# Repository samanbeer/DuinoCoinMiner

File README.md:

# DuinoCoinMiner

- **What is it?** It is a small PCB board with XIAO ESP32-C3 as main MCU for controlling 6 ATmega328P chips
- **What does it do?** It mines crypto currency called Duino Coin. Which is a specialized coin that can be mined on any device like arduinos and lot more. You read about it on their [site](duinocoin.com)

## Project Gallery

### 3D PCB Renders

### PCB Schematic and layout

### 3D Enclosure (Fusion 360)

*3D printable case made in Fusion 360. All CAD and 3D model files (`.f3z`, `.step`) are in the [`CAD/`](CAD/) folder.*

---

### Required Tools & Materials

- Soldering iron
- Good solder wire
- Solder flux 
- small tweezers for picking small components like resistors and condenzators 
- 3D Printer for printing case from /cad folder

### Assembly Steps

1. **Start with the chips:**
   
   - **ATmega328P-AU** and **BSS138PS** .
   - It is best to solder these first while the board is clear of other bigger things.

2. **SMD Components:**
- - C1–C18, C31, C32 
  - C19–C30 
  - C33
  - R1–R10
3. **Main MCU:**
-     **Seeed Studio XIAO ESP32-C3**.
  - Solder the XIAO directly onto the PCB pads or solder pin headers so you can plug it in(not recommended)
4. **THT Components:**
-     **Crystals:** 20MHz crystals. Clip the leads, and solder from the bottom side.
  - **Switches:** 6x6mm reset buttons. Snap them into their holes and solder.
  - **ISP pin Header:** 2x3 pin header. Solder it to the board.
5. **Enclosure Assembly:**
-     3D print the bottom base (`case.step`) and the lid (`case_lid.step`). Files are in the /CAD folder.
  - Place PCB inside the bottom enclosure, with XIAO USB-C port aligned to the hole, and attach the lid.

---

## Firmware

Firmware files are located in "firmware" folder with README.md that contains guide how to flash the chips correclty and what you will need to install.

## BOM

| Reference               | amount | Value / Component          | Footprint / Package      | Link                                                                                                    | Cost (USD) |
| ----------------------- |:------:|:-------------------------- |:------------------------ |:------------------------------------------------------------------------------------------------------- |:----------:|
| **C1-C18, C31 and C32** | 20     | 100nF 50V                  | 0603 SMD                 | [TME Link](https://www.tme.eu/cz/details/0603b104k500ct/kondenzatory-mlcc-smd/walsin/)                  | $0.40      |
| **C19-C30**             | 12     | 22pF 50V                   | 0603 SMD                 | [TME Link](https://www.tme.eu/cz/details/cc0603jrnpo9bn220/kondenzatory-mlcc-smd/yageo/)                | $0.36      |
| **C33**                 | 1      | 10µF 10V                   | 0603 SMD                 | [TME Link](https://www.tme.eu/cz/details/lmk107bj106maltd/kondenzatory-mlcc-smd/taiyo-yuden/)           | $0.12      |
| **J1**                  | 1      | 2x3 Pin Header             | Pin header 2x03 (2.54mm) | [TME Link](https://www.tme.eu/cz/details/bl2-06g/dutinkove-listy/connfly/)                              | $0.35      |
| **Q1**                  | 1      | BSS138PS mosfet            | SOT-363                  | [TME Link](https://www.tme.eu/cz/details/bss138ps.115/tranzistory-s-polem-n-kanalove-smd/nexperia/)     | $0.45      |
| **R1-R10**              | 10     | 10kΩ                       | 0805 SMD                 | [TME Link](https://www.tme.eu/cz/details/crcw080510k0fkea/rezistory-smd/vishay/)                        | $0.14      |
| **SW1–SW6**             | 6      | Switch (6x6mm, Height=5mm) | SW_PUSH_6mm_H5mm THT     | [TME Link](https://www.tme.eu/cz/details/1825910-6/mikroprepninace-tact-tht/te-connectivity/)           | $0.90      |
| **U1**                  | 1      | Seeed Studio XIAO ESP32-C3 | XIAO DIP/SMD Module      | [TME Link](https://www.tme.eu/cz/details/seeed-113991054/vyvojove-kity-ostatni/seeed-studio/113991054/) | $6.36      |
| **U2-U7**               | 6      | ATmega328P-AU (**20mHz**)  | TQFP-32                  | [TME Link](https://www.tme.eu/cz/details/atmega328p-au/mikrokontrolery-avr/microchip-technology/)       | $14.70     |
| **Y1-Y6**               | 6      | 20MHz Quartz Crystal       | HC-49/U THT              | [TME Link](https://www.tme.eu/cz/details/49-20.000maaj-b/krystalove-rezonatory-tht/qst/)                | $1.80      |
| **PCB**                 | 1      | 2 Layers                   |                          | [JLCPCB](https://jlcpcb.com)                                                                            | ±$14       |
| **Shipping**            |        | Total Shipping             |                          | TME and JLCPCB                                                                                          | $12.9      |
| **Total**               |        |                            |                          |                                                                                                         | **52.48**  |

JLCPCB cart:

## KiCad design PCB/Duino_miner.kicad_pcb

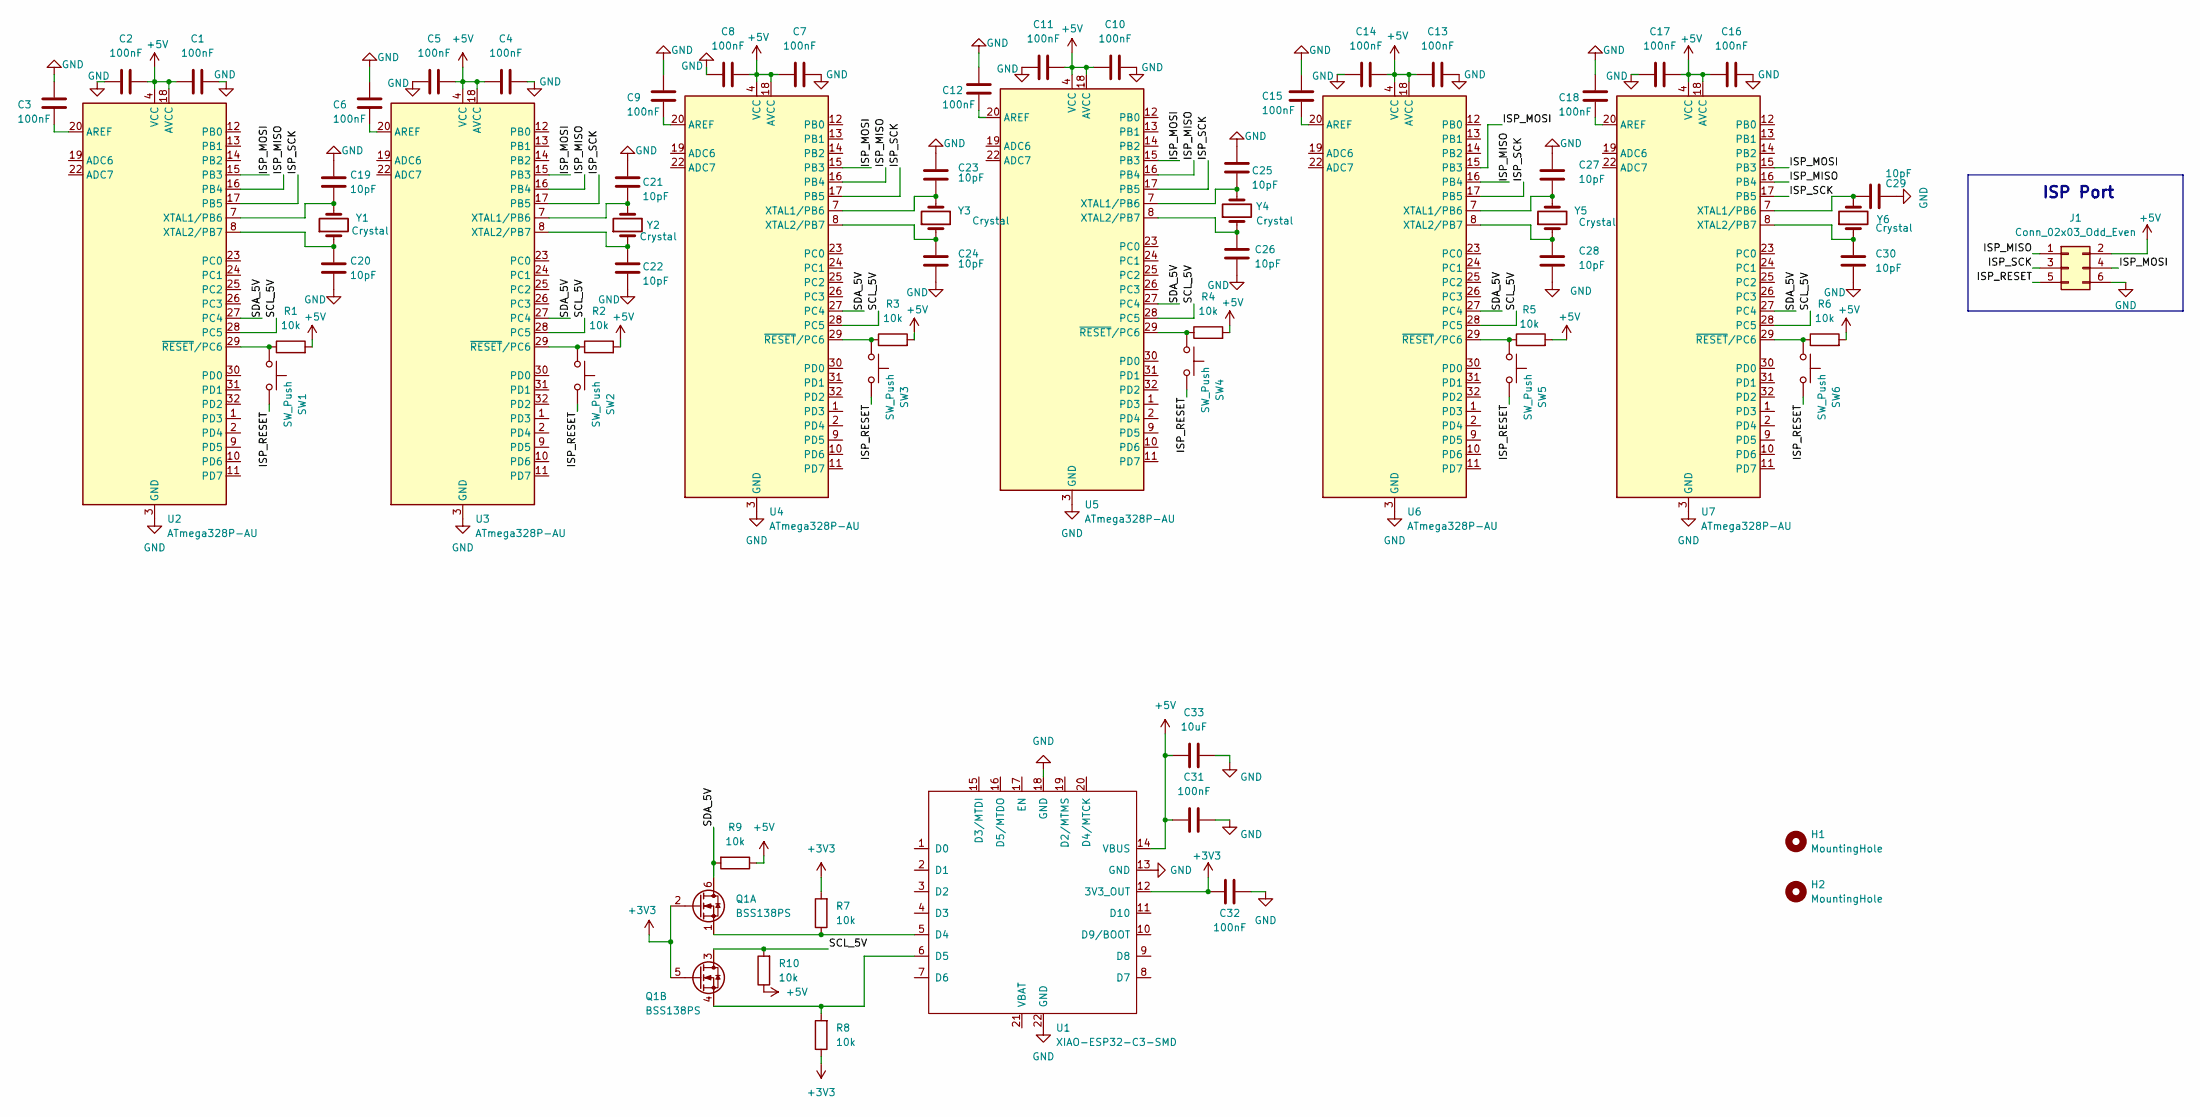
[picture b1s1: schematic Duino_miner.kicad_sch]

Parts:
C1, C2, C3, C4, C5, C6, C7, C8, C9, C10, C11, C12, C13, C14, C15, C16, C17, C18, C31, C32: 100nF; C_0603_1608Metric_Pad1.08x0.95mm_HandSolder
C19, C20, C21, C22, C23, C24, C25, C26, C27, C28, C29, C30: 10pF; C_0603_1608Metric_Pad1.08x0.95mm_HandSolder
C33: 10uF; C_0603_1608Metric_Pad1.08x0.95mm_HandSolder
H1, H2: MountingHole; MountingHole_2mm
J1: Conn_02x03_Odd_Even; PinSocket_2x03_P2.54mm_Vertical
Q1: BSS138PS; SOT-363_SC-70-6
R1, R2, R3, R4, R5, R6, R7, R8, R9, R10: 10k; R_0805_2012Metric_Pad1.20x1.40mm_HandSolder
SW1, SW2, SW3, SW4, SW5, SW6: SW_Push; SW_PUSH_6mm_H5mm
U1: XIAO-ESP32-C3-SMD; XIAO-ESP32-C3-DIP-SMD
U2, U3, U4, U5, U6, U7: ATmega328P-AU; TQFP-32_7x7mm_P0.8mm
Y1, Y2, Y3, Y4, Y5, Y6: Crystal; Crystal_HC49-4H_Vertical

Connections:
+3V3: C32.1, Q1.2 (G), Q1.5 (G), R7.2, R8.1, U1.12 (3V3_OUT)
+5V: C1.1, C2.2, C4.1, C5.2, C7.1, C8.2, C10.1, C11.2, C13.1, C14.2, C16.1, C17.2, C31.1, C33.1, J1.2, R1.2, R2.2, R3.2, R4.2, R5.2, R6.2, R9.1, R10.1, U1.14 (VBUS), U2.4 (VCC), U2.6 (VCC), U2.18 (AVCC), U3.4 (VCC), U3.6 (VCC), U3.18 (AVCC), U4.4 (VCC), U4.6 (VCC), U4.18 (AVCC), U5.4 (VCC), U5.6 (VCC), U5.18 (AVCC), U6.4 (VCC), U6.6 (VCC), U6.18 (AVCC), U7.4 (VCC), U7.6 (VCC), U7.18 (AVCC)
/ISP_MISO: J1.1, U2.16 (PB4), U3.16 (PB4), U4.16 (PB4), U5.16 (PB4), U6.16 (PB4), U7.16 (PB4)
/ISP_MOSI: J1.4, U2.15 (PB3), U3.15 (PB3), U4.15 (PB3), U5.15 (PB3), U6.15 (PB3), U7.15 (PB3)
/ISP_RESET: J1.5, SW1.2, SW2.2, SW3.2, SW4.2, SW5.2, SW6.2
/ISP_SCK: J1.3, U2.17 (PB5), U3.17 (PB5), U4.17 (PB5), U5.17 (PB5), U6.17 (PB5), U7.17 (PB5)
/SCL_5V: Q1.3 (D), R10.2, U2.28 (PC5), U3.28 (PC5), U4.28 (PC5), U5.28 (PC5), U6.28 (PC5), U7.28 (PC5)
/SDA_5V: Q1.6 (D), R9.2, U2.27 (PC4), U3.27 (PC4), U4.27 (PC4), U5.27 (PC4), U6.27 (PC4), U7.27 (PC4)
GND: C1.2, C2.1, C3.1, C4.2, C5.1, C6.1, C7.2, C8.1, C9.1, C10.2, C11.1, C12.1, C13.2, C14.1, C15.1, C16.2, C17.1, C18.1, C19.2, C20.1, C21.2, C22.1, C23.2, C24.1, C25.2, C26.1, C27.2, C28.1, C29.2, C30.1, C31.2, C32.2, C33.2, J1.6, U1.13 (GND), U1.18 (GND), U1.22 (GND), U2.3 (GND), U2.5 (GND), U2.21 (GND), U3.3 (GND), U3.5 (GND), U3.21 (GND), U4.3 (GND), U4.5 (GND), U4.21 (GND), U5.3 (GND), U5.5 (GND), U5.21 (GND), U6.3 (GND), U6.5 (GND), U6.21 (GND), U7.3 (GND), U7.5 (GND), U7.21 (GND)
unnamed: Q1.1 (S), R7.1, U1.5 (D4)
unnamed: Q1.4 (S), R8.2, U1.6 (D5)
unnamed: C3.2, U2.20 (AREF)
unnamed: C19.1, U2.7 (XTAL1/PB6), Y1.2
unnamed: C20.2, U2.8 (XTAL2/PB7), Y1.1
unnamed: R1.1, SW1.1, U2.29 (~RESET/PC6)
unnamed: C6.2, U3.20 (AREF)
unnamed: C21.1, U3.7 (XTAL1/PB6), Y2.2
unnamed: C22.2, U3.8 (XTAL2/PB7), Y2.1
unnamed: R2.1, SW2.1, U3.29 (~RESET/PC6)
unnamed: C9.2, U4.20 (AREF)
unnamed: C23.1, U4.7 (XTAL1/PB6), Y3.2
unnamed: C24.2, U4.8 (XTAL2/PB7), Y3.1
unnamed: R3.1, SW3.1, U4.29 (~RESET/PC6)
unnamed: C12.2, U5.20 (AREF)
unnamed: C25.1, U5.7 (XTAL1/PB6), Y4.2
unnamed: C26.2, U5.8 (XTAL2/PB7), Y4.1
unnamed: R4.1, SW4.1, U5.29 (~RESET/PC6)
unnamed: C15.2, U6.20 (AREF)
unnamed: C27.1, U6.7 (XTAL1/PB6), Y5.2
unnamed: C28.2, U6.8 (XTAL2/PB7), Y5.1
unnamed: R5.1, SW5.1, U6.29 (~RESET/PC6)
unnamed: C18.2, U7.20 (AREF)
unnamed: C29.1, U7.7 (XTAL1/PB6), Y6.2
unnamed: C30.2, U7.8 (XTAL2/PB7), Y6.1
unnamed: R6.1, SW6.1, U7.29 (~RESET/PC6)

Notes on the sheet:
ISP Port

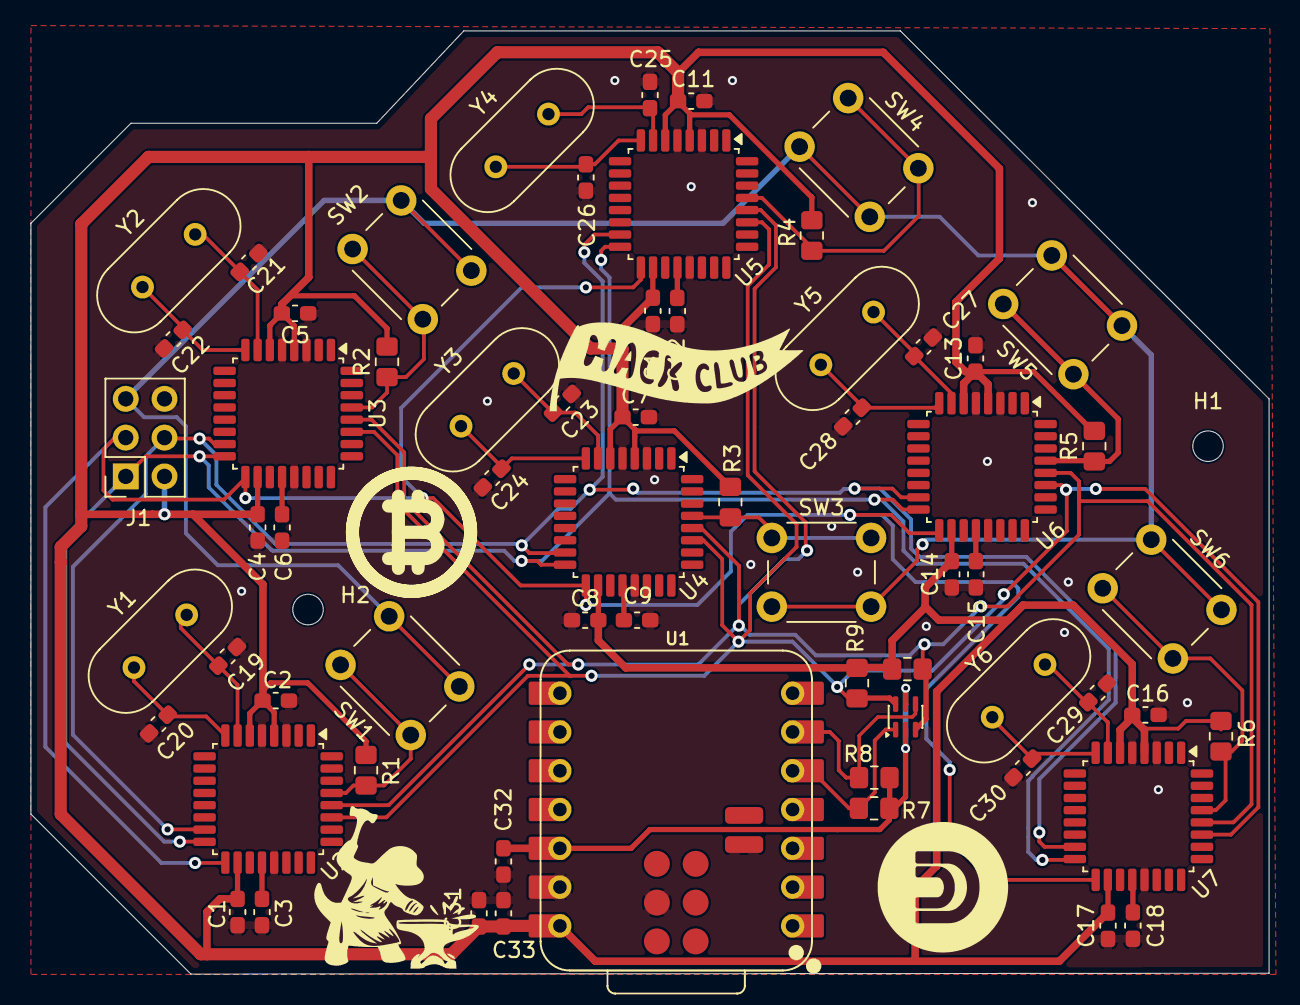
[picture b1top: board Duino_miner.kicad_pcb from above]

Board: 2 copper layers, 81.1 x 61.8 mm, 66 parts (0 on the bottom side), 35 nets.
